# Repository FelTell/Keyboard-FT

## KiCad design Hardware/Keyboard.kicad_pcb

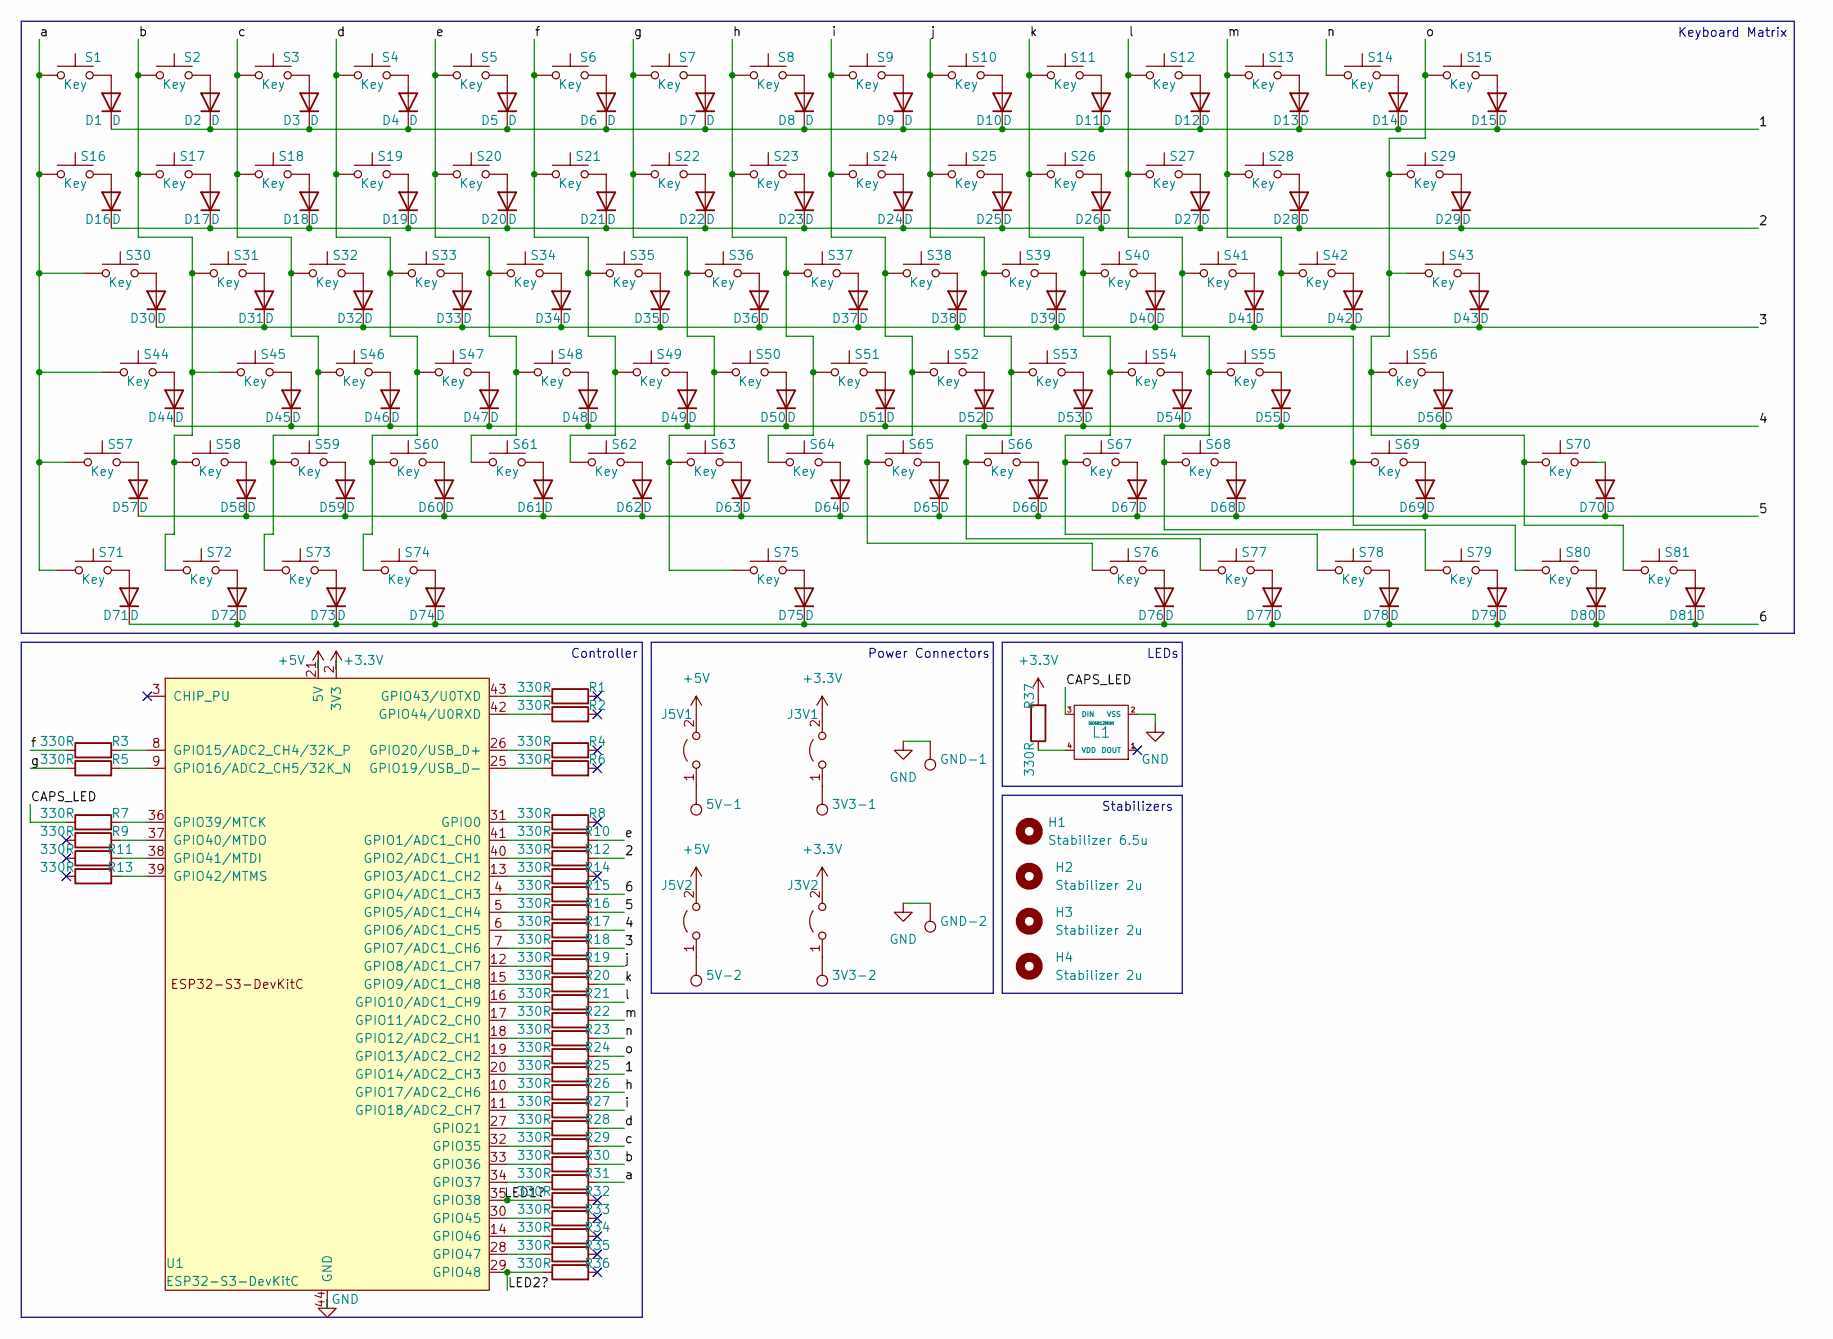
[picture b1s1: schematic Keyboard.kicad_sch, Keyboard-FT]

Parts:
3V3-1, 3V3-2, 5V-1, 5V-2: TestPoint; PinHeader_1x01_P1.00mm_Vertical
D1, D2, D3, D4, D5, D6, D7, D8, D9, D10, D11, D12, D13, D14, D15, D16, D17, D18, D19, D20, D21, D22, D23, D24, D25, D26, D27, D28, D29, D30, D31, D32, D33, D34, D35, D36, D37, D38, D39, D40, D41, D42, D43, D44, D45, D46, D47, D48, D49, D50, D51, D52, D53, D54, D55, D56, D57, D58, D59, D60, D61, D62, D63, D64, D65, D66, D67, D68, D69, D70, D71, D72, D73, D74, D75, D76, D77, D78, D79, D80, D81: D; D3_TH_SMD_v2
GND-1, GND-2: TestPoint; PinHeader_1x01_P1.00mm_Vertical
H1: Stabilizer 6.5u; Stabilizer_Cherry_MX_6.25u
H2, H3, H4: Stabilizer 2u; Stabilizer_Cherry_MX_2.00u
J3V1, J3V2, J5V1, J5V2: Jumper_2_Open; SolderJumper-2_P1.3mm_Open_TrianglePad1.0x1.5mm
L1: SK6812MINI; SK6812MINI_rev
R1, R2, R3, R4, R5, R6, R7, R8, R9, R10, R11, R12, R13, R14, R15, R16, R17, R18, R19, R20, R21, R22, R23, R24, R25, R26, R27, R28, R29, R30, R31, R32, R33, R34, R35, R36, R37: 330R; R_0603_1608Metric_Pad0.98x0.95mm_HandSolder
S1, S2, S3, S4, S5, S6, S7, S8, S9, S10, S11, S12, S13, S14, S15, S16, S17, S18, S19, S20, S21, S22, S23, S24, S25, S26, S27, S28, S31, S32, S33, S34, S35, S36, S37, S38, S39, S40, S41, S42, S45, S46, S47, S48, S49, S50, S51, S52, S53, S54, S55, S58, S59, S60, S61, S62, S63, S64, S65, S66, S67, S68, S70, S72, S73, S74, S77, S79, S80, S81: Key; SW_Cherry_MX_PCB_1.00u
S29: Key; SW_Cherry_MX_PCB_2.00u
S30, S43: Key; SW_Cherry_MX_PCB_1.50u
S44: Key; SW_Cherry_MX_PCB_1.75u
S56: Key; SW_Cherry_MX_PCB_2.25u
S57, S71, S76, S78: Key; SW_Cherry_MX_PCB_1.25u
S69: Key; SW_Cherry_MX_PCB_2.75u
S75: Key; SW_Cherry_MX_PCB_6.25u
U1: ESP32-S3-DevKitC

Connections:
+3.3V: J3V1.2 (B), J3V2.2 (B), R37.2, U1.1 (3V3), U1.2 (3V3)
+5V: J5V1.2 (B), J5V2.2 (B), U1.21 (5V)
/1: D1.1 (K), D2.1 (K), D3.1 (K), D4.1 (K), D5.1 (K), D6.1 (K), D7.1 (K), D8.1 (K), D9.1 (K), D10.1 (K), D11.1 (K), D12.1 (K), D13.1 (K), D14.1 (K), D15.1 (K), R25.2
/2: D16.1 (K), D17.1 (K), D18.1 (K), D19.1 (K), D20.1 (K), D21.1 (K), D22.1 (K), D23.1 (K), D24.1 (K), D25.1 (K), D26.1 (K), D27.1 (K), D28.1 (K), D29.1 (K), R12.2
/3: D30.1 (K), D31.1 (K), D32.1 (K), D33.1 (K), D34.1 (K), D35.1 (K), D36.1 (K), D37.1 (K), D38.1 (K), D39.1 (K), D40.1 (K), D41.1 (K), D42.1 (K), D43.1 (K), R18.2
/4: D44.1 (K), D45.1 (K), D46.1 (K), D47.1 (K), D48.1 (K), D49.1 (K), D50.1 (K), D51.1 (K), D52.1 (K), D53.1 (K), D54.1 (K), D55.1 (K), D56.1 (K), R17.2
/5: D57.1 (K), D58.1 (K), D59.1 (K), D60.1 (K), D61.1 (K), D62.1 (K), D63.1 (K), D64.1 (K), D65.1 (K), D66.1 (K), D67.1 (K), D68.1 (K), D69.1 (K), D70.1 (K), R16.2
/6: D71.1 (K), D72.1 (K), D73.1 (K), D74.1 (K), D75.1 (K), D76.1 (K), D77.1 (K), D78.1 (K), D79.1 (K), D80.1 (K), D81.1 (K), R15.2
/CAPS_LED: L1.3 (DIN), R7.1
/LED1?: R32.1, U1.35 (GPIO38)
/LED2?: R36.1, U1.29 (GPIO48)
/a: R31.2, S1.1, S16.1, S30.1, S44.1, S57.1, S71.1
/b: R30.2, S2.1, S17.1, S31.1, S45.1, S58.1, S72.1
/c: R29.2, S3.1, S18.1, S32.1, S46.1, S59.1, S73.1
/d: R28.2, S4.1, S19.1, S33.1, S47.1, S60.1, S74.1
/e: R10.2, S5.1, S20.1, S34.1, S48.1, S61.1
/f: R3.1, S6.1, S21.1, S35.1, S49.1, S62.1
/g: R5.1, S7.1, S22.1, S36.1, S50.1, S63.1, S75.1
/h: R26.2, S8.1, S23.1, S37.1, S51.1, S64.1
/i: R27.2, S9.1, S24.1, S38.1, S52.1, S65.1, S76.1
/j: R19.2, S10.1, S25.1, S39.1, S53.1, S66.1, S77.1
/k: R20.2, S11.1, S26.1, S40.1, S54.1, S67.1, S78.1
/l: R21.2, S12.1, S27.1, S41.1, S55.1, S68.1, S79.1
/m: R22.2, S13.1, S28.1, S42.1, S69.1, S80.1
/n: R23.2, S14.1
/o: R24.2, S15.1, S29.1, S43.1, S56.1, S70.1, S81.1
GND: GND-1.1, GND-2.1, L1.2 (VSS), U1.22 (GND), U1.23 (GND), U1.24 (GND), U1.44 (GND); also elsewhere on the board
unnamed: D1.2 (A), S1.2
unnamed: D2.2 (A), S2.2
unnamed: D3.2 (A), S3.2
unnamed: D4.2 (A), S4.2
unnamed: D5.2 (A), S5.2
unnamed: D6.2 (A), S6.2
unnamed: D7.2 (A), S7.2
unnamed: D8.2 (A), S8.2
unnamed: D9.2 (A), S9.2
unnamed: D10.2 (A), S10.2
unnamed: D11.2 (A), S11.2
unnamed: D12.2 (A), S12.2
unnamed: D13.2 (A), S13.2
unnamed: D14.2 (A), S14.2
unnamed: D15.2 (A), S15.2
unnamed: D16.2 (A), S16.2
unnamed: D17.2 (A), S17.2
unnamed: D18.2 (A), S18.2
unnamed: D19.2 (A), S19.2
unnamed: D20.2 (A), S20.2
unnamed: D21.2 (A), S21.2
unnamed: D22.2 (A), S22.2
unnamed: D23.2 (A), S23.2
unnamed: D24.2 (A), S24.2
unnamed: D25.2 (A), S25.2
unnamed: D26.2 (A), S26.2
unnamed: D27.2 (A), S27.2
unnamed: D28.2 (A), S28.2
unnamed: D29.2 (A), S29.2
unnamed: D30.2 (A), S30.2
unnamed: D31.2 (A), S31.2
unnamed: D32.2 (A), S32.2
unnamed: D33.2 (A), S33.2
unnamed: D34.2 (A), S34.2
unnamed: D35.2 (A), S35.2
unnamed: D36.2 (A), S36.2
unnamed: D37.2 (A), S37.2
unnamed: D38.2 (A), S38.2
unnamed: D39.2 (A), S39.2
unnamed: D40.2 (A), S40.2
unnamed: D41.2 (A), S41.2
unnamed: D42.2 (A), S42.2
unnamed: D43.2 (A), S43.2
unnamed: D44.2 (A), S44.2
unnamed: D45.2 (A), S45.2
unnamed: D46.2 (A), S46.2
unnamed: D47.2 (A), S47.2
unnamed: D48.2 (A), S48.2
unnamed: D49.2 (A), S49.2
unnamed: D50.2 (A), S50.2
unnamed: D51.2 (A), S51.2
unnamed: D52.2 (A), S52.2
unnamed: D53.2 (A), S53.2
unnamed: D54.2 (A), S54.2
unnamed: D55.2 (A), S55.2
unnamed: D56.2 (A), S56.2
unnamed: D57.2 (A), S57.2
unnamed: D58.2 (A), S58.2
unnamed: D59.2 (A), S59.2
unnamed: D60.2 (A), S60.2
unnamed: D61.2 (A), S61.2
unnamed: D62.2 (A), S62.2
unnamed: D63.2 (A), S63.2
unnamed: D64.2 (A), S64.2
unnamed: D65.2 (A), S65.2
unnamed: D66.2 (A), S66.2
unnamed: D67.2 (A), S67.2
unnamed: D68.2 (A), S68.2
unnamed: D69.2 (A), S69.2
unnamed: D70.2 (A), S70.2
unnamed: D71.2 (A), S71.2
unnamed: D72.2 (A), S72.2
unnamed: D73.2 (A), S73.2
unnamed: D74.2 (A), S74.2
unnamed: D75.2 (A), S75.2
unnamed: D76.2 (A), S76.2
unnamed: D77.2 (A), S77.2
unnamed: D78.2 (A), S78.2
unnamed: D79.2 (A), S79.2
unnamed: D80.2 (A), S80.2
unnamed: D81.2 (A), S81.2
unnamed 108: 3V3-1.1, J3V1.1 (A); also elsewhere on the board
unnamed: 3V3-2.1, J3V2.1 (A)
unnamed 110: 5V-1.1, J5V1.1 (A); also elsewhere on the board
unnamed: 5V-2.1, J5V2.1 (A)
unnamed: L1.4 (VDD), R37.1
unnamed: R8.1, U1.31 (GPIO0)
unnamed: R10.1, U1.41 (GPIO1/ADC1_CH0)
unnamed: R12.1, U1.40 (GPIO2/ADC1_CH1)
unnamed: R14.1, U1.13 (GPIO3/ADC1_CH2)
unnamed: R15.1, U1.4 (GPIO4/ADC1_CH3)
unnamed: R16.1, U1.5 (GPIO5/ADC1_CH4)
unnamed: R17.1, U1.6 (GPIO6/ADC1_CH5)
unnamed: R18.1, U1.7 (GPIO7/ADC1_CH6)
unnamed: R19.1, U1.12 (GPIO8/ADC1_CH7)
unnamed: R20.1, U1.15 (GPIO9/ADC1_CH8)
unnamed: R21.1, U1.16 (GPIO10/ADC1_CH9)
unnamed: R22.1, U1.17 (GPIO11/ADC2_CH0)
unnamed: R23.1, U1.18 (GPIO12/ADC2_CH1)
unnamed: R24.1, U1.19 (GPIO13/ADC2_CH2)
unnamed: R25.1, U1.20 (GPIO14/ADC2_CH3)
unnamed: R3.2, U1.8 (GPIO15/ADC2_CH4/32K_P)
unnamed: R5.2, U1.9 (GPIO16/ADC2_CH5/32K_N)
unnamed: R26.1, U1.10 (GPIO17/ADC2_CH6)
unnamed: R27.1, U1.11 (GPIO18/ADC2_CH7)
unnamed: R6.1, U1.25 (GPIO19/USB_D-)
unnamed: R4.1, U1.26 (GPIO20/USB_D+)
unnamed: R28.1, U1.27 (GPIO21)
unnamed: R29.1, U1.32 (GPIO35)
unnamed: R30.1, U1.33 (GPIO36)
unnamed: R31.1, U1.34 (GPIO37)
unnamed: R7.2, U1.36 (GPIO39/MTCK)
unnamed: R9.2, U1.37 (GPIO40/MTDO)
unnamed: R11.2, U1.38 (GPIO41/MTDI)
unnamed: R13.2, U1.39 (GPIO42/MTMS)
unnamed: R1.1, U1.43 (GPIO43/U0TXD)
unnamed: R2.1, U1.42 (GPIO44/U0RXD)
unnamed: R33.1, U1.30 (GPIO45)
unnamed: R34.1, U1.14 (GPIO46)
unnamed: R35.1, U1.28 (GPIO47)

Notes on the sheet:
Keyboard Matrix
Controller
Power Connectors
LEDs
Stabilizers

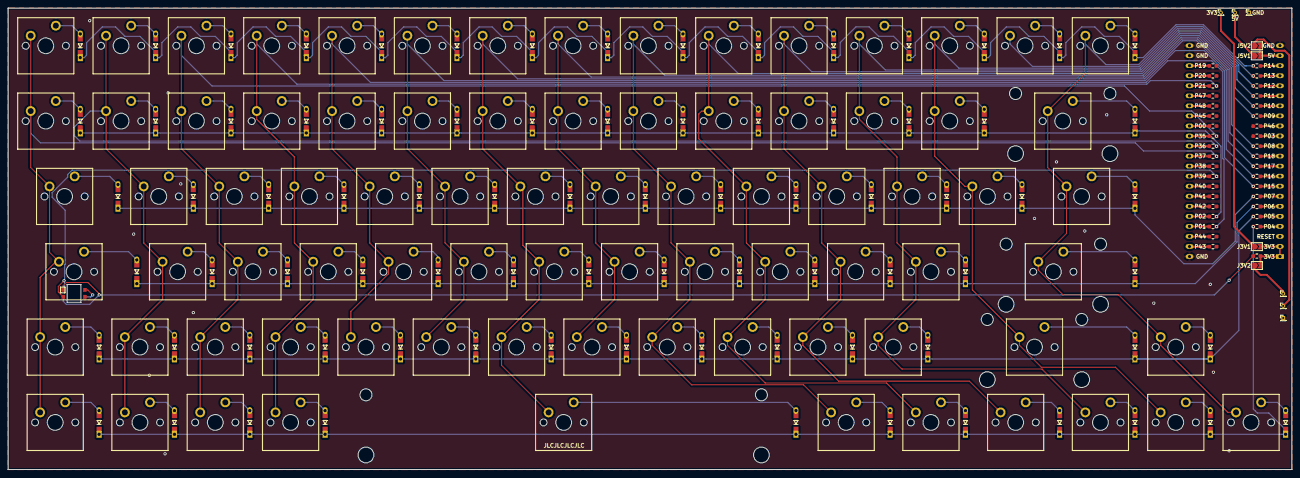
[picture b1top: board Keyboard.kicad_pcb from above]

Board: 2 copper layers, 324.6 x 116.6 mm, 215 parts (1 on the bottom side), 147 nets.

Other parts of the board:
3V3, 5V: TestPoint; PinHeader_1x01_P1.00mm_Vertical
GND: TestPoint; PinHeader_1x01_P1.00mm_Vertical

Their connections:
GND: GND.1; also elsewhere on the board
unnamed 108: 3V3.1; also elsewhere on the board
unnamed 110: 5V.1; also elsewhere on the board

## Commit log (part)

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2023-07-16 cube init
2023-07-16 added some configuration files
2023-07-16 Cmake configuration
2024-01-10 usb hid test
2024-01-10 hardware init
2024-01-10 finished tracing
2024-01-21 sch changes
2024-01-21 added tracks
2024-01-23 final hardware
2024-01-23 fixed name
2024-01-23 added gebers
2024-01-24 fixed output files
2024-02-05 backups
2024-02-05 removed old fw
2024-02-05 uodated git ignore
2024-02-05 project renaming
2024-02-05 fixed minor disalignment
2024-02-06 added components
2024-02-06 only keyboard example
2024-02-06 working led
2024-02-06 updated git ignore
2024-02-06 added status led task
2024-02-06 git cache reset
2024-02-10 improved status led
2024-02-13 matrix start
2024-02-14 added keys to matrix
2024-02-22 List in matrix. Added key and layout headers
2024-02-22 added usb hid
2024-02-22 updated log
2024-02-22 improved report
2024-02-22 fixed stuck key
2024-02-22 showing caps led
2024-02-22 polling disconnect
2024-02-22 removed warnings
2024-02-25 updated names
2024-02-27 added matrix delay to ensure proper gpio timing fixed not sending modifiers and keys
2024-02-27 Fixed layout
2024-02-27 removed unnecessary code
2024-02-28 added caps leds renamed namespace to just led
2024-02-28 start supporting function key
2024-02-28 added roadmap
2024-03-02 added working /? key
2024-03-02 added consumer usage support
2024-03-02 fixed wrong caps led when connecting
2024-03-02 fixed fn key
2024-03-02 improved keyboard reliability by:
    - matrix now updates keys once every cycle and has a higher polling rate
    - Report is now sent every 10 ms or when matrix is updated
2024-03-02 added timer class
2024-03-02 waiting for queue message to send report
2024-03-13 added next/previous media fn
2024-03-16 minor formatting
2024-03-16 Added support to call function using fn key, allowing commands inside keyboard
2024-03-16 added led brightness adjust
2024-03-16 rainbow now keep the same period in all brightness level
2024-03-16 renamed statusled file to leds
2024-03-16 sending report every 100 ms to prevent stuck keys when a device has been woken up by the keyboard
2024-03-16 fixed some fn commands not working
2024-04-03 improved variable naming
2024-04-03 updated roadmap
2024-04-03 improved polling
2024-04-03 added controller and logic to switch between usb and ble
2024-04-24 added event group to rtos utils
2024-04-24 added some precompiler verification for rtos utils
2024-04-24 added max bits guard on events groups. improved briefs
2024-04-25 improved task related class, briefs and functions
2024-04-25 improved timer functions. Deleting FromIsr functions and integrating it in a single function
2024-04-25 improved queues
2024-06-08 improved rtosutils
2024-08-18 working ble using example
2024-08-18 added unified report
2024-08-18 rename controller
2024-08-18 some cleaning
2025-03-12 Added improved rtosUtils
2025-03-12 implemented LED timeout
2025-10-27 added deboucing, removed poll delay
2025-12-17 increased debounce count
2025-12-18 Updated esp-idf version
2025-12-31 improved debounce algorithm to reduce delay
2026-02-06 updated debounce counts
2026-05-03 fixed wrong led command when multiple command are sent.
